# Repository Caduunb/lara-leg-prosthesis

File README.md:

# lara-leg-prosthesis devel branch

LARA Leg Prosthesis is a rehabilitation project whose goal is to design an active control system for above knee amputees using Gait Cycle Identification using Deep Learning.

Stable versions of code are uploaded here. On-progress codes are uploaded in the devel branch.

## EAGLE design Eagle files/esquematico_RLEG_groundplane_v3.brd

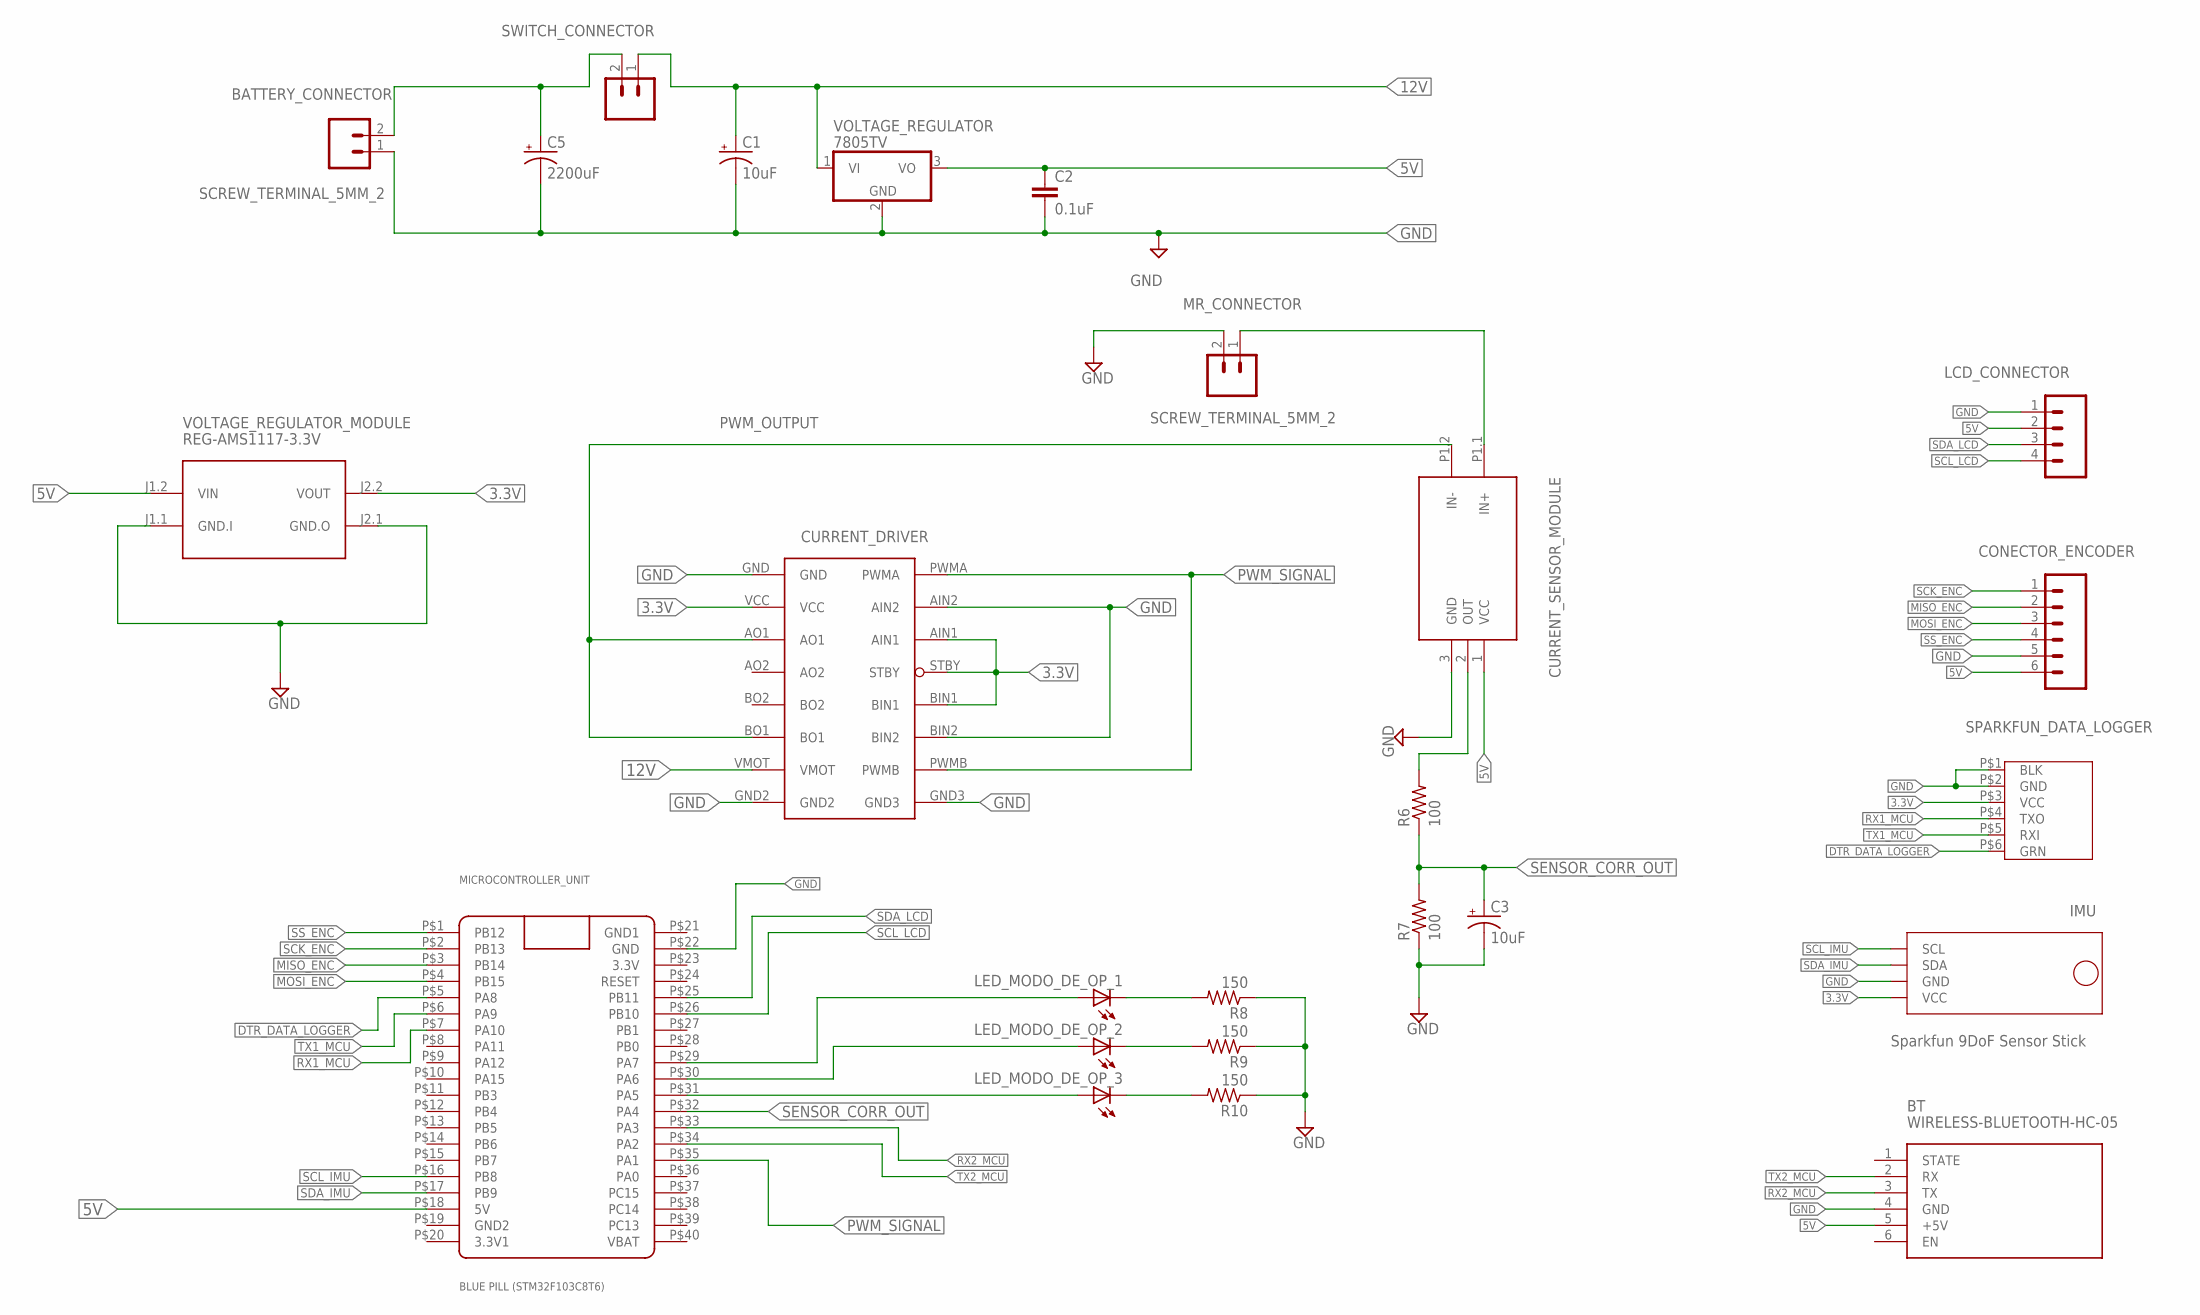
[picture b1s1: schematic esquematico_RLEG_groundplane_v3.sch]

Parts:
BATTERY_CONNECTOR: SCREW_TERMINAL_5MM_2; SCREWTERMINAL-5MM-2
BT: WIRELESS-BLUETOOTH-HC-05
C1, C3: 10uF; E5-5
C2: 0.1uF; C2.5-4
C5: 2200uF; E5-13
CONECTOR_ENCODER: a; MOLEX-1X6
CURRENT_DRIVER: TB6612FNG
CURRENT_SENSOR_MODULE: CURRENT-SENSOR-ACS712#IC
IMU: Sparkfun 9DoF Sensor Stick; IMU
LCD_CONNECTOR: CONN_04POLAR; MOLEX-1X4
LED_MODO_DE_OP_1, LED_MODO_DE_OP_2, LED_MODO_DE_OP_3: LED3MM
MICROCONTROLLER_UNIT: BLUE PILL (STM32F103C8T6); BLUE_PILL
MR_CONNECTOR: SCREW_TERMINAL_5MM_2; SCREWTERMINAL-5MM-2
R6, R7: 100; 0207/9
R8, R9, R10: 150; 0207/9
SPARKFUN_DATA_LOGGER: DATA_LOGGER
SWITCH_CONNECTOR: CONN_02POLAR; MOLEX-1X2
VOLTAGE_REGULATOR: 7805TV; TO220V
VOLTAGE_REGULATOR_MODULE: REG-AMS1117-3.3V; REG-AMS1117

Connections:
3.3V: CURRENT_DRIVER.AIN1, CURRENT_DRIVER.BIN1, CURRENT_DRIVER.STBY, CURRENT_DRIVER.VCC, IMU.VCC, SPARKFUN_DATA_LOGGER.P$3 (VCC), VOLTAGE_REGULATOR_MODULE.J2.2 (VOUT)
5V: BT.5 (+5V), C2.1, CONECTOR_ENCODER.6, CURRENT_SENSOR_MODULE.1 (VCC), LCD_CONNECTOR.2, MICROCONTROLLER_UNIT.P$18 (5V), VOLTAGE_REGULATOR.3 (VO), VOLTAGE_REGULATOR_MODULE.J1.2 (VIN)
12V: C1.+, CURRENT_DRIVER.VMOT, SWITCH_CONNECTOR.1, VOLTAGE_REGULATOR.1 (VI)
DTR_DATA_LOGGER: MICROCONTROLLER_UNIT.P$5 (PA8), SPARKFUN_DATA_LOGGER.P$6 (GRN)
GND: BATTERY_CONNECTOR.1, BT.4 (GND), C1.-, C2.2, C3.-, C5.-, CONECTOR_ENCODER.5, CURRENT_DRIVER.AIN2, CURRENT_DRIVER.BIN2, CURRENT_DRIVER.GND, CURRENT_DRIVER.GND2, CURRENT_DRIVER.GND3, CURRENT_SENSOR_MODULE.3 (GND), IMU.GND, LCD_CONNECTOR.1, MICROCONTROLLER_UNIT.P$22 (GND), MR_CONNECTOR.2, R7.1, R8.1, R9.1, R10.1, SPARKFUN_DATA_LOGGER.P$1 (BLK), SPARKFUN_DATA_LOGGER.P$2 (GND), VOLTAGE_REGULATOR.2 (GND), VOLTAGE_REGULATOR_MODULE.J1.1 (GND.I), VOLTAGE_REGULATOR_MODULE.J2.1 (GND.O)
GND1: MICROCONTROLLER_UNIT.P$21 (GND1)
MISO_ENC: CONECTOR_ENCODER.2, MICROCONTROLLER_UNIT.P$3 (PB14)
MOSI_ENC: CONECTOR_ENCODER.3, MICROCONTROLLER_UNIT.P$4 (PB15)
unnamed: CURRENT_SENSOR_MODULE.P1.1 (IN+), MR_CONNECTOR.1
unnamed: BATTERY_CONNECTOR.2, C5.+, SWITCH_CONNECTOR.2
unnamed: LED_MODO_DE_OP_2.A, MICROCONTROLLER_UNIT.P$30 (PA6)
unnamed: LED_MODO_DE_OP_1.A, MICROCONTROLLER_UNIT.P$29 (PA7)
unnamed: LED_MODO_DE_OP_3.A, MICROCONTROLLER_UNIT.P$31 (PA5)
unnamed: LED_MODO_DE_OP_1.K (C), R8.2
unnamed: LED_MODO_DE_OP_2.K (C), R9.2
unnamed: LED_MODO_DE_OP_3.K (C), R10.2
unnamed: CURRENT_SENSOR_MODULE.2 (OUT), R6.2
PWM_OUTPUT: CURRENT_DRIVER.AO1, CURRENT_DRIVER.BO1, CURRENT_SENSOR_MODULE.P1.2 (IN-)
PWM_SIGNAL: CURRENT_DRIVER.PWMA, CURRENT_DRIVER.PWMB, MICROCONTROLLER_UNIT.P$35 (PA1)
RX1_MCU: MICROCONTROLLER_UNIT.P$7 (PA10), SPARKFUN_DATA_LOGGER.P$4 (TXO)
RX2_MCU: BT.3 (TX), MICROCONTROLLER_UNIT.P$33 (PA3)
SCK_ENC: CONECTOR_ENCODER.1, MICROCONTROLLER_UNIT.P$2 (PB13)
SCL_IMU: IMU.SCL, MICROCONTROLLER_UNIT.P$16 (PB8)
SCL_LCD: LCD_CONNECTOR.4, MICROCONTROLLER_UNIT.P$26 (PB10)
SDA_IMU: IMU.SDA, MICROCONTROLLER_UNIT.P$17 (PB9)
SDA_LCD: LCD_CONNECTOR.3, MICROCONTROLLER_UNIT.P$25 (PB11)
SENSOR_CORR_OUT: C3.+, MICROCONTROLLER_UNIT.P$32 (PA4), R6.1, R7.2
SS_ENC: CONECTOR_ENCODER.4, MICROCONTROLLER_UNIT.P$1 (PB12)
TX1_MCU: MICROCONTROLLER_UNIT.P$6 (PA9), SPARKFUN_DATA_LOGGER.P$5 (RXI)
TX2_MCU: BT.2 (RX), MICROCONTROLLER_UNIT.P$34 (PA2)

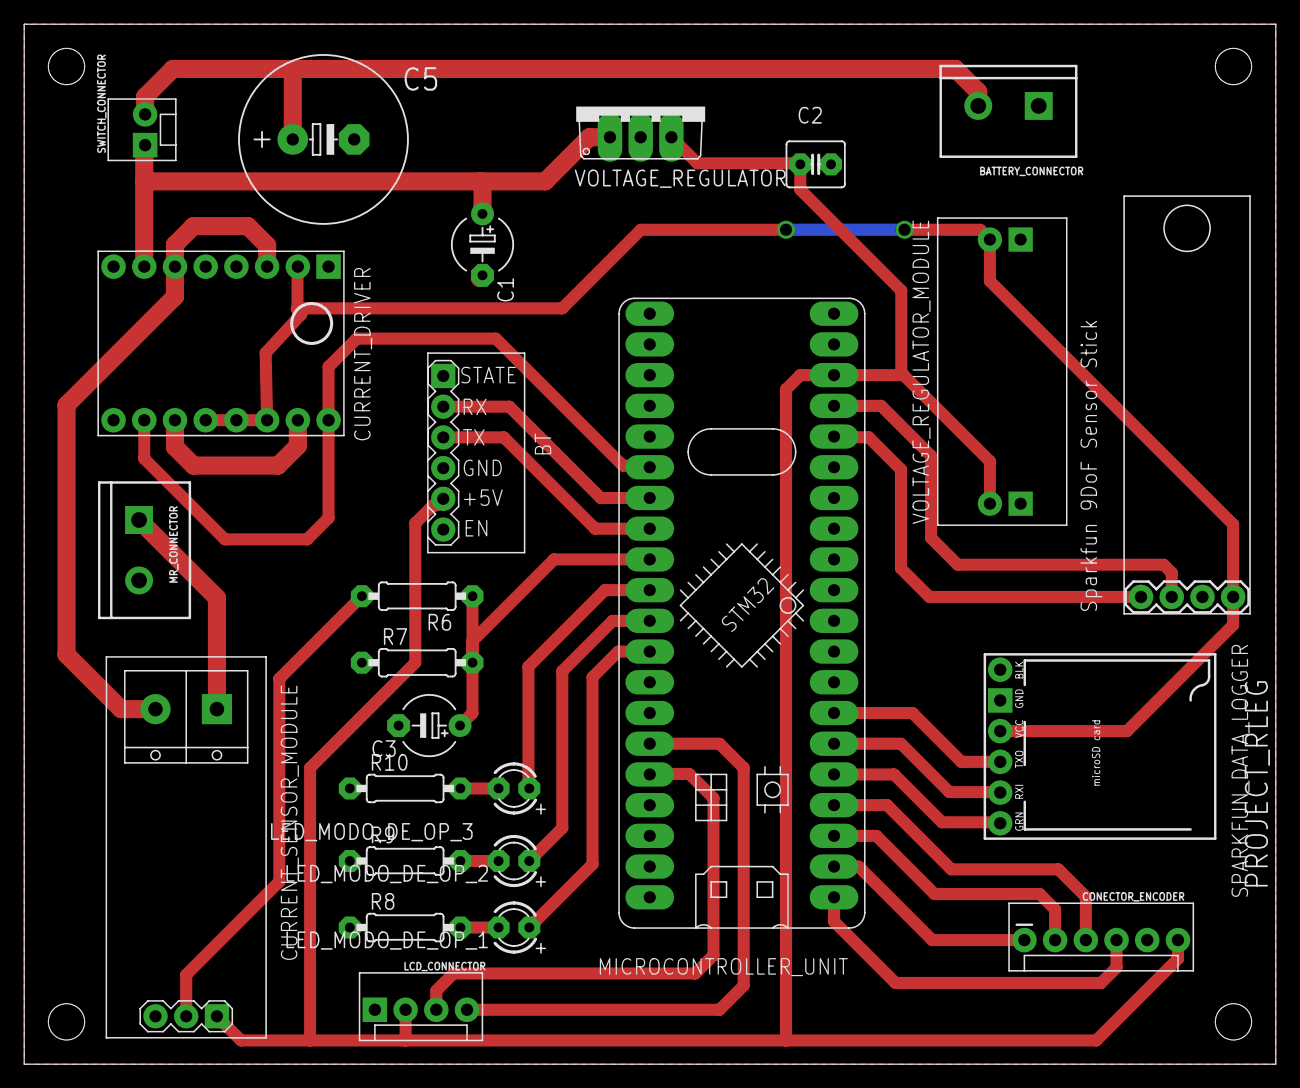
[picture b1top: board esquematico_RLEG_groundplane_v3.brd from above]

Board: 2 copper layers, 103.5 x 86.0 mm, 25 parts (0 on the bottom side), 29 nets.

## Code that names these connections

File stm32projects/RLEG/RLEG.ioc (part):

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Mcu.Name=STM32F103C(8-B)Tx
Mcu.Package=LQFP48
Mcu.UserName=STM32F103C8Tx
PA1.GPIOParameters=GPIO_Label
PA1.GPIO_Label=PWM_SIGNAL
PA1.Signal=GPIO_Output
PA10.GPIOParameters=GPIO_Label
PA10.GPIO_Label=TX_DATA_LOGGER
PA10.Mode=Asynchronous
PA10.Signal=USART1_RX
PA11.Mode=CTS_RTS
PA11.Signal=USART1_CTS
PA12.Mode=CTS_RTS
PA12.Signal=USART1_RTS
PA13.Mode=Serial_Wire
PA13.Signal=SYS_JTMS-SWDIO
PA14.Mode=Serial_Wire
PA14.Signal=SYS_JTCK-SWCLK
PA2.GPIOParameters=GPIO_Label
PA2.GPIO_Label=RX_BT
PA2.Mode=Asynchronous
PA2.Signal=USART2_TX
PA3.GPIOParameters=GPIO_Label
PA3.GPIO_Label=TX_BT
PA3.Mode=Asynchronous
PA3.Signal=USART2_RX
PA4.GPIOParameters=GPIO_Label
PA4.GPIO_Label=CURRENT_SENSOR_IN
PA4.Signal=SharedAnalog_PA4
PA5.GPIOParameters=PinState,GPIO_Label
PA5.GPIO_Label=LED_A5
PA5.PinState=GPIO_PIN_RESET
PA5.Signal=GPIO_Output
PA6.GPIOParameters=PinState,GPIO_Label
PA6.GPIO_Label=LED_A6
PA6.PinState=GPIO_PIN_RESET
PA6.Signal=GPIO_Output
PA7.GPIOParameters=PinState,GPIO_Label
PA7.GPIO_Label=LED_A7
PA7.PinState=GPIO_PIN_RESET
PA7.Signal=GPIO_Output
PA8.GPIOParameters=GPIO_Label
PA8.GPIO_Label=DTR_DATA_LOGGER
PA8.Signal=GPIO_Output
PA9.GPIOParameters=GPIO_Label
PA9.GPIO_Label=RX_DATA_LOGGER
PA9.Mode=Asynchronous
PA9.Signal=USART1_TX
PB10.GPIOParameters=GPIO_Label
PB10.GPIO_Label=SCL_LCD
PB10.Mode=I2C
PB10.Signal=I2C2_SCL
PB11.GPIOParameters=GPIO_Label
PB11.GPIO_Label=SDA_LCD
PB11.Mode=I2C
PB11.Signal=I2C2_SDA
PB12.GPIOParameters=GPIO_Label
PB12.GPIO_Label=SS_ENC
PB12.Mode=NSS_Signal_Hard_Output
PB12.Signal=SPI2_NSS
PB13.GPIOParameters=GPIO_Label
PB13.GPIO_Label=SCK_ENC
PB13.Mode=Full_Duplex_Master
PB13.Signal=SPI2_SCK
PB14.GPIOParameters=GPIO_Label
PB14.GPIO_Label=MISO_ENC
PB14.Mode=Full_Duplex_Master
PB14.Signal=SPI2_MISO
PB15.GPIOParameters=GPIO_Label
PB15.GPIO_Label=MOSI_ENC
PB15.Mode=Full_Duplex_Master
PB15.Signal=SPI2_MOSI
PB8.GPIOParameters=GPIO_Label
PB8.GPIO_Label=SCL_IMU
PB8.Mode=I2C
PB8.Signal=I2C1_SCL
PB9.GPIOParameters=GPIO_Label
PB9.GPIO_Label=SDA_IMU
PB9.Mode=I2C
PB9.Signal=I2C1_SDA
PD0-OSC_IN.Mode=HSE-External-Oscillator
PD0-OSC_IN.Signal=RCC_OSC_IN
PD1-OSC_OUT.Mode=HSE-External-Oscillator
PD1-OSC_OUT.Signal=RCC_OSC_OUT
RCC.SYSCLKFreq_VALUE=72000000
RCC.SYSCLKSource=RCC_SYSCLKSOURCE_PLLCLK
board=custom

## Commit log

2019-04-30 eagle_files_30_04_19
2019-04-30 Eagle files
2019-05-08 arquivos eagle atualizados
2019-05-08 adicionando codigos arduino
2019-05-08 adicionando codigos e bibliotecas arduino
2019-05-22 Create empty
2019-05-22 debug drivers, and source codes
2019-05-27 adicionando arquivos de documentacao e do ambiente sw4stm32
2019-05-31 Create ADXL345
2019-05-31 Create ADXL_OPENLOG
2019-05-31 Create a
2019-05-31 upload de codigos funcionais e bibliotecas
2019-05-31 master branch fix
2019-05-31 deleting debug folder
2019-06-03 adding imu and rleg projects
2019-06-05 update main with encoder
    Not working.
2019-06-06 encoder funcionando
2019-06-12 imu updated complete
2019-06-12 imu update files
2019-06-12 projeto completo imu e rleg
2019-06-12 codigos imu6050
2019-06-12 mpu6050 demo
2019-06-13 led blink renamed
2019-06-13 adicionando arquivos de documentacao
2019-06-13 mpu6050 working
2019-06-13 mpu6050 scaled data
2019-06-19 adding freertos files
2019-06-23 system id routine with changes
2019-06-28 adding control by threshold
2019-06-29 uploading control by ang velocity threshold
2019-06-30 adding current sensor experiment routine
2019-07-16 adding control by threshold angular velocity program
2019-07-16 adding encoder data read program
2019-07-16 adding pwm generation program
2019-07-16 fixing readme pwm generation file
2019-07-16 adding adc read program
2019-07-16 adding system identification program
2019-07-16 adding systemidentification2 project
2019-07-16 adding documented files
2019-08-09 adding documentation files to master

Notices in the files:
parts and their libraries:
SparkFun-Connectors: Licensing: Creative Commons ShareAlike 4.0 International - https://creativecommons.org/licenses/by-sa/4.0
diy-modules: Released under the Creative Commons Attribution 4.0 International License: http://creativecommons.org/licenses/by/4.0
